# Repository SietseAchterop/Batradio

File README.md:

# Batradio
Software defined radio on rpi zero

The goal of this project is to create a simple sdr using a rpi-zero and a simple hat.
It should work to up to 150kHz, to be used as a ULF radio or bat detector.

## Hat for raspberry Pi

### batradio_pcb
contains a KiCad project for a hat for the rpi (zero).
It contains a 1Mbit 16 bit spi adc, mcp33131 and a 14 bit dac, mcp4821.
Also a preamplifier and lowpass filter.

Status: The prototype had the following error in the PCB design. Pins 1 and 8 of the U4, a ths4521, should be swapped and a 100nF capacitor to ground should be connected to pin 2.
This, untested, version corrects that.

Here the 

And the PCB

## Kernel module, a failed attempt.

Kernel module to process the data from adc and dac.
This also is work in progress.
Currently I have not been able to get the FIQ interrupt working.

### mcp331131_streaming

A variant of https://iosoft.blog/2020/11/16/streaming-analog-data-raspberry-pi/

The main changes for the 16 bit mcp33131 are:

  - Used PWM to create the CNVST pulse.
  - Writing dummy to create SCLK.
  - added -U option to send data over UDP channel.
  - DAC not used yet.
  
Basically works, but the data is partly wrong.
Also the SPI clock should be lower than 5 MHz?

## kicadlibs
My local symbols and footprints for KiCad

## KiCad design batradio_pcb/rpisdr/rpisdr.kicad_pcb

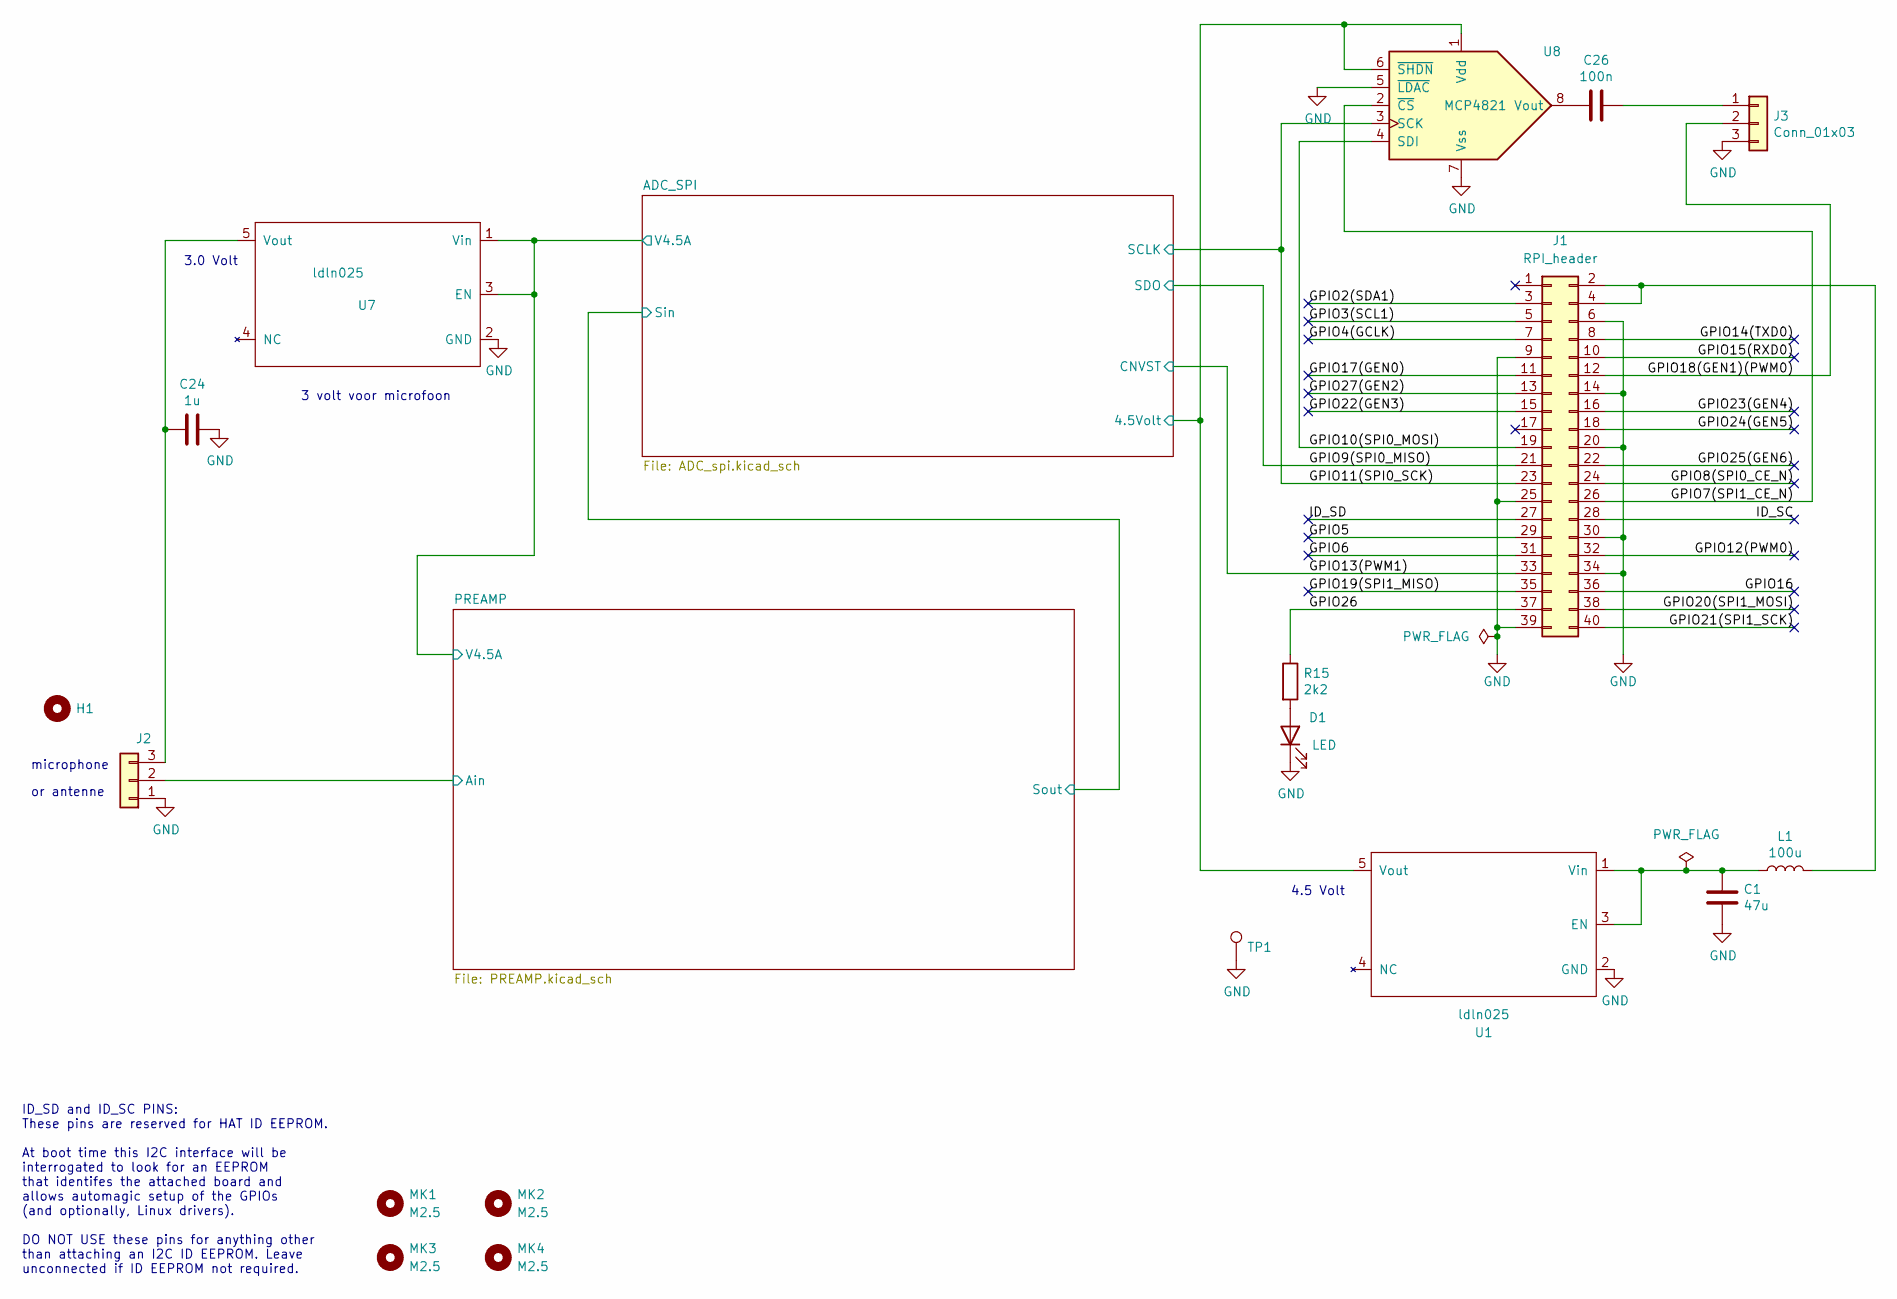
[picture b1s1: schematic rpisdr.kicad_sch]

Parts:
C1: 47u; CP_EIA-7343-30_AVX-N
C24: 1u; C_1206_3216Metric_Pad1.33x1.80mm_HandSolder
C26: 100n; C_0805_2012Metric_Pad1.18x1.45mm_HandSolder
D1: LED; LED_0805_2012Metric
H1: MountingHole; MountingHole_2.5mm
J1: RPI_header; PinHeader_2x20_P2.54mm_Vertical
J2, J3: Conn_01x03; PinHeader_1x03_P2.54mm_Vertical_SMD_Pin1Left
L1: 100u; L_1812_4532Metric_Pad1.30x3.40mm_HandSolder
MK1, MK2, MK3, MK4: M2.5; MountingHole_2.7mm_M2.5
R15: 2k2; R_0805_2012Metric_Pad1.20x1.40mm_HandSolder
TP1: TestPoint; TestPoint_Loop_D2.50mm_Drill1.0mm
U1, U7: ldln025; SOT-23-5
U8: MCP4821; MSOP-8_3x3mm_P0.65mm

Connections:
/ADC_SPI/4.5Volt: U1.5 (Vout), U8.1 (Vdd), U8.6 (~SHDN); also elsewhere on the board
/ADC_SPI/V4.5A: U7.1 (Vin), U7.3 (EN); also elsewhere on the board
/GPIO2(SDA1): J1.3
/GPIO3(SCL1): J1.5
/GPIO4(GCLK): J1.7
/GPIO5: J1.29
/GPIO6: J1.31
/GPIO7(SPI1_CE_N): J1.26, U8.2 (~CS)
/GPIO8(SPI0_CE_N): J1.24
/GPIO9(SPI0_MISO): J1.21; also elsewhere on the board
/GPIO10(SPI0_MOSI): J1.19, U8.4 (SDI)
/GPIO11(SPI0_SCK): J1.23, U8.3 (SCK); also elsewhere on the board
/GPIO12(PWM0): J1.32
/GPIO13(PWM1): J1.33; also elsewhere on the board
/GPIO14(TXD0): J1.8
/GPIO15(RXD0): J1.10
/GPIO16: J1.36
/GPIO17(GEN0): J1.11
/GPIO18(GEN1)(PWM0): J1.12, J3.2
/GPIO19(SPI1_MISO): J1.35
/GPIO20(SPI1_MOSI): J1.38
/GPIO21(SPI1_SCK): J1.40
/GPIO22(GEN3): J1.15
/GPIO23(GEN4): J1.16
/GPIO24(GEN5): J1.18
/GPIO25(GEN6): J1.22
/GPIO26: J1.37, R15.1
/GPIO27(GEN2): J1.13
/ID_SC: J1.28
/ID_SD: J1.27
/PREAMP/Ain: J2.2; also elsewhere on the board
GND: C1.2, C24.1, D1.1 (K), J1.6, J1.9, J1.14, J1.20, J1.25, J1.30, J1.34, J1.39, J2.1, J3.3, TP1.1, U1.2 (GND), U7.2 (GND), U8.5 (~LDAC), U8.7 (Vss); also elsewhere on the board
unnamed: D1.2 (A), R15.2
unnamed: J1.2, J1.4, L1.2
unnamed: C24.2, J2.3, U7.5 (Vout)
unnamed: C26.1, J3.1
unnamed: C1.1, L1.1, U1.1 (Vin), U1.3 (EN)
unnamed: C26.2, U8.8 (Vout)

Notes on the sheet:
microphone
or antenne
ID_SD and ID_SC PINS: These pins are reserved for HAT ID EEPROM. At boot time this I2C interface will be interrogated to look for an EEPROM that identifes the attached board and allows automagic setup of the GPIOs (and optionally, Linux drivers). DO NOT USE these pins for anything other than attach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
3 volt voor microfoon
3.0 Volt
4.5 Volt

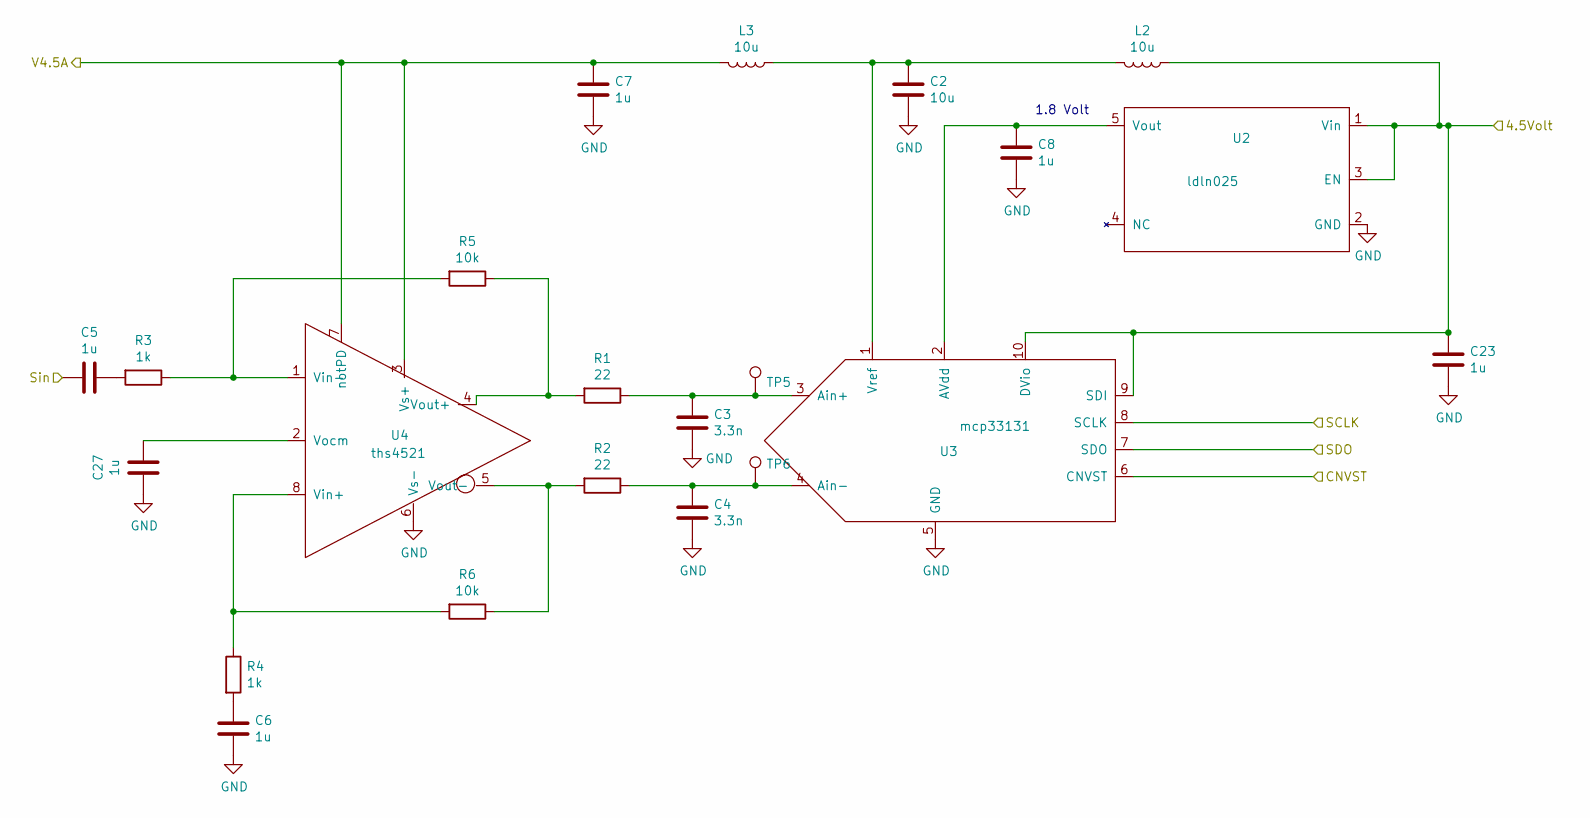
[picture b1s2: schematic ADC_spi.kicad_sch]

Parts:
C2: 10u; CP_EIA-3528-12_Kemet-T
C3, C4: 3.3n; C_0805_2012Metric_Pad1.18x1.45mm_HandSolder
C5, C6, C7, C8, C23, C27: 1u; C_1206_3216Metric_Pad1.33x1.80mm_HandSolder
L2, L3: 10u; L_1812_4532Metric_Pad1.30x3.40mm_HandSolder
R1, R2: 22; R_0805_2012Metric_Pad1.20x1.40mm_HandSolder
R3, R4: 1k; R_0805_2012Metric_Pad1.20x1.40mm_HandSolder
R5, R6: 10k; R_0805_2012Metric_Pad1.20x1.40mm_HandSolder
TP5, TP6: TestPoint; TestPoint_Pad_2.0x2.0mm
U2: ldln025; SOT-23-5
U3: mcp33131; MSOP-10_3x3mm_P0.5mm
U4: ths4521; VSSOP-8_3x3mm_P0.65mm

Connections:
/ADC_SPI/4.5Volt: C23.1, L2.1, U2.1 (Vin), U2.3 (EN), U3.9 (SDI), U3.10 (DVio); also elsewhere on the board
/ADC_SPI/Sin: C5.2; also elsewhere on the board
/ADC_SPI/V4.5A: C7.1, L3.2, U4.3 (Vs+), U4.7 (notPD); also elsewhere on the board
/GPIO9(SPI0_MISO): U3.7 (SDO); also elsewhere on the board
/GPIO11(SPI0_SCK): U3.8 (SCLK); also elsewhere on the board
/GPIO13(PWM1): U3.6 (CNVST); also elsewhere on the board
GND: C2.2, C3.2, C4.2, C6.2, C7.2, C8.2, C23.2, C27.2, U2.2 (GND), U3.5 (GND), U4.6 (Vs-); also elsewhere on the board
unnamed: C5.1, R3.2
unnamed: C6.1, R4.2
unnamed: C8.1, U2.5 (Vout), U3.2 (AVdd)
unnamed: C3.1, R1.1, TP5.1, U3.3 (Ain+)
unnamed: C4.1, R2.1, TP6.1, U3.4 (Ain-)
unnamed: C2.1, L2.2, L3.1, U3.1 (Vref)
unnamed: R4.1, R6.2, U4.8 (Vin+)
unnamed: R3.1, R5.2, U4.1 (Vin-)
unnamed: C27.1, U4.2 (Vocm)
unnamed: R1.2, R5.1, U4.4 (Vout+)
unnamed: R2.2, R6.1, U4.5 (Vout-)

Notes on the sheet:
1.8 Volt

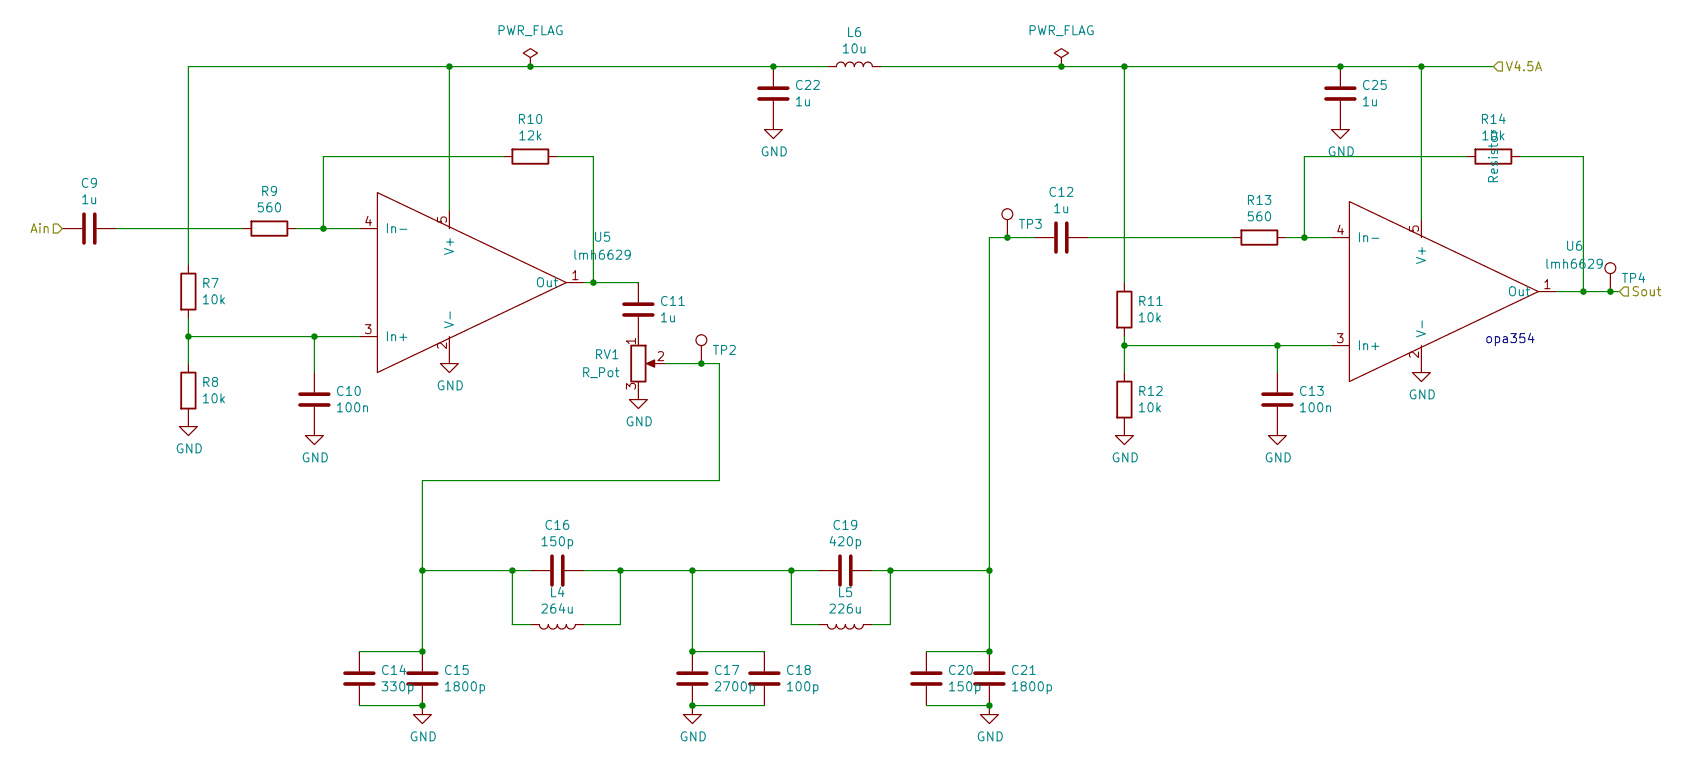
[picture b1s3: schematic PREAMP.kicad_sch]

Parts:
C9, C11, C12, C22, C25: 1u; C_1206_3216Metric_Pad1.33x1.80mm_HandSolder
C10, C13: 100n; C_0805_2012Metric_Pad1.18x1.45mm_HandSolder
C14: 330p; C_0805_2012Metric_Pad1.18x1.45mm_HandSolder
C15, C21: 1800p; C_0805_2012Metric_Pad1.18x1.45mm_HandSolder
C16, C20: 150p; C_0805_2012Metric_Pad1.18x1.45mm_HandSolder
C17: 2700p; C_0805_2012Metric_Pad1.18x1.45mm_HandSolder
C18: 100p; C_0805_2012Metric_Pad1.18x1.45mm_HandSolder
C19: 420p; C_0805_2012Metric_Pad1.18x1.45mm_HandSolder
L4: 264u; L_Neosid_Ms95
L5: 226u; L_Neosid_Ms95
L6: 10u; L_1812_4532Metric_Pad1.30x3.40mm_HandSolder
R7, R8, R11, R12, R14: 10k; R_0805_2012Metric_Pad1.20x1.40mm_HandSolder
R9, R13: 560; R_0805_2012Metric_Pad1.20x1.40mm_HandSolder
R10: 12k; R_0805_2012Metric_Pad1.20x1.40mm_HandSolder
RV1: R_Pot; Potentiometer_Bourns_3214J_Horizontal
TP2, TP3, TP4: TestPoint; TestPoint_Pad_2.0x2.0mm
U5, U6: lmh6629; SOT-23-5

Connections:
/ADC_SPI/Sin: R14.1, TP4.1, U6.1 (Out); also elsewhere on the board
/ADC_SPI/V4.5A: C25.1, L6.2, R11.1, U6.5 (V+); also elsewhere on the board
/PREAMP/Ain: C9.2; also elsewhere on the board
GND: C10.2, C13.2, C14.2, C15.2, C17.2, C18.2, C20.2, C21.2, C22.2, C25.2, R8.2, R12.2, RV1.3, U5.2 (V-), U6.2 (V-); also elsewhere on the board
unnamed: C9.1, R9.2
unnamed: C11.2, RV1.1
unnamed: C12.1, R13.2
unnamed: C12.2, C19.1, C20.1, C21.1, L5.1, TP3.1
unnamed: C14.1, C15.1, C16.2, L4.2, RV1.2, TP2.1
unnamed: C16.1, C17.1, C18.1, C19.2, L4.1, L5.2
unnamed: C10.1, R7.2, R8.1, U5.3 (In+)
unnamed: R9.1, R10.2, U5.4 (In-)
unnamed: C11.1, R10.1, U5.1 (Out)
unnamed: C22.1, L6.1, R7.1, U5.5 (V+)
unnamed: C13.1, R11.2, R12.1, U6.3 (In+)
unnamed: R13.1, R14.2, U6.4 (In-)

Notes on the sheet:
opa354

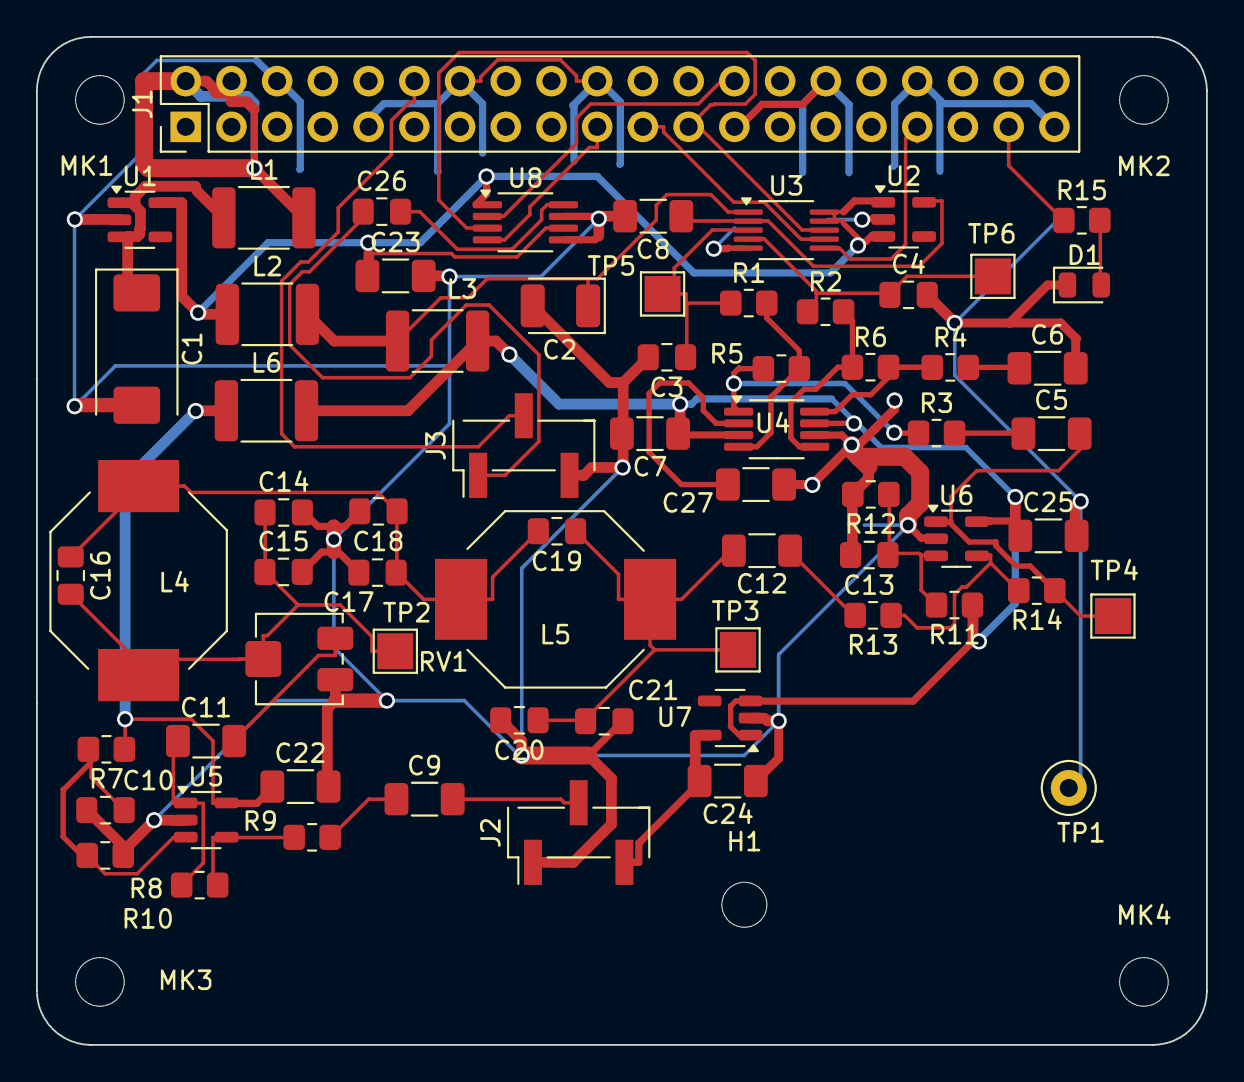
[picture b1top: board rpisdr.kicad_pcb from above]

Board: 2 copper layers, 65.0 x 56.0 mm, 72 parts (0 on the bottom side), 41 nets.

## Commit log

2020-03-23 Added README.md
2020-03-23 Added test program tst.c
2020-03-25 Created testprogram tst5.c
2020-04-04 Add alloctest.c
2020-04-04 Simplified alloctest.c
2020-04-04 Simplify alloctest.c
2020-04-06 add testfiqtimer.c
2020-04-09 Added fiqtest.c
2020-04-13 patched fiqtest.c
2020-04-19 Added fiqtest_2.c
2020-04-28 Added fiqtest_3.c
2020-06-01 Update repository
2020-06-04 Added fiqtest_4.c
2024-02-06 Added mcp331131 version of streaming from iosoft.
2024-02-10 Update rpi_adc_stream
2026-03-22 Corrected schematic and added mykicadlibs
2026-03-24 Corrected mylib library settings
2026-04-24 Updated mykicadlibs
